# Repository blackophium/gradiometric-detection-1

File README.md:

# gradiometric-detection-1
Gradiometric detection of heart rate - analog model.

This is a project of PCB which includes:

- 10.7 MHZ sine generator (transmitting coil),
- place for receive a signal from receiver coil,
- synchronous demodulation,
- transmitting signal filtration.

How it works:

The generator transmits a signal to a transmitting coil, which is applied to the patient's chest. 
The carrier signal is received along with the wave signal from the mechanical operation of the heart through receiver coils arranged in an anti-parallel way. 
Then the signal is demodulated and filtered (we filter out the constant component of the carrier wave 10.7MHz). 

The resulting signal is a medium disturbance originating in the patient's chest.

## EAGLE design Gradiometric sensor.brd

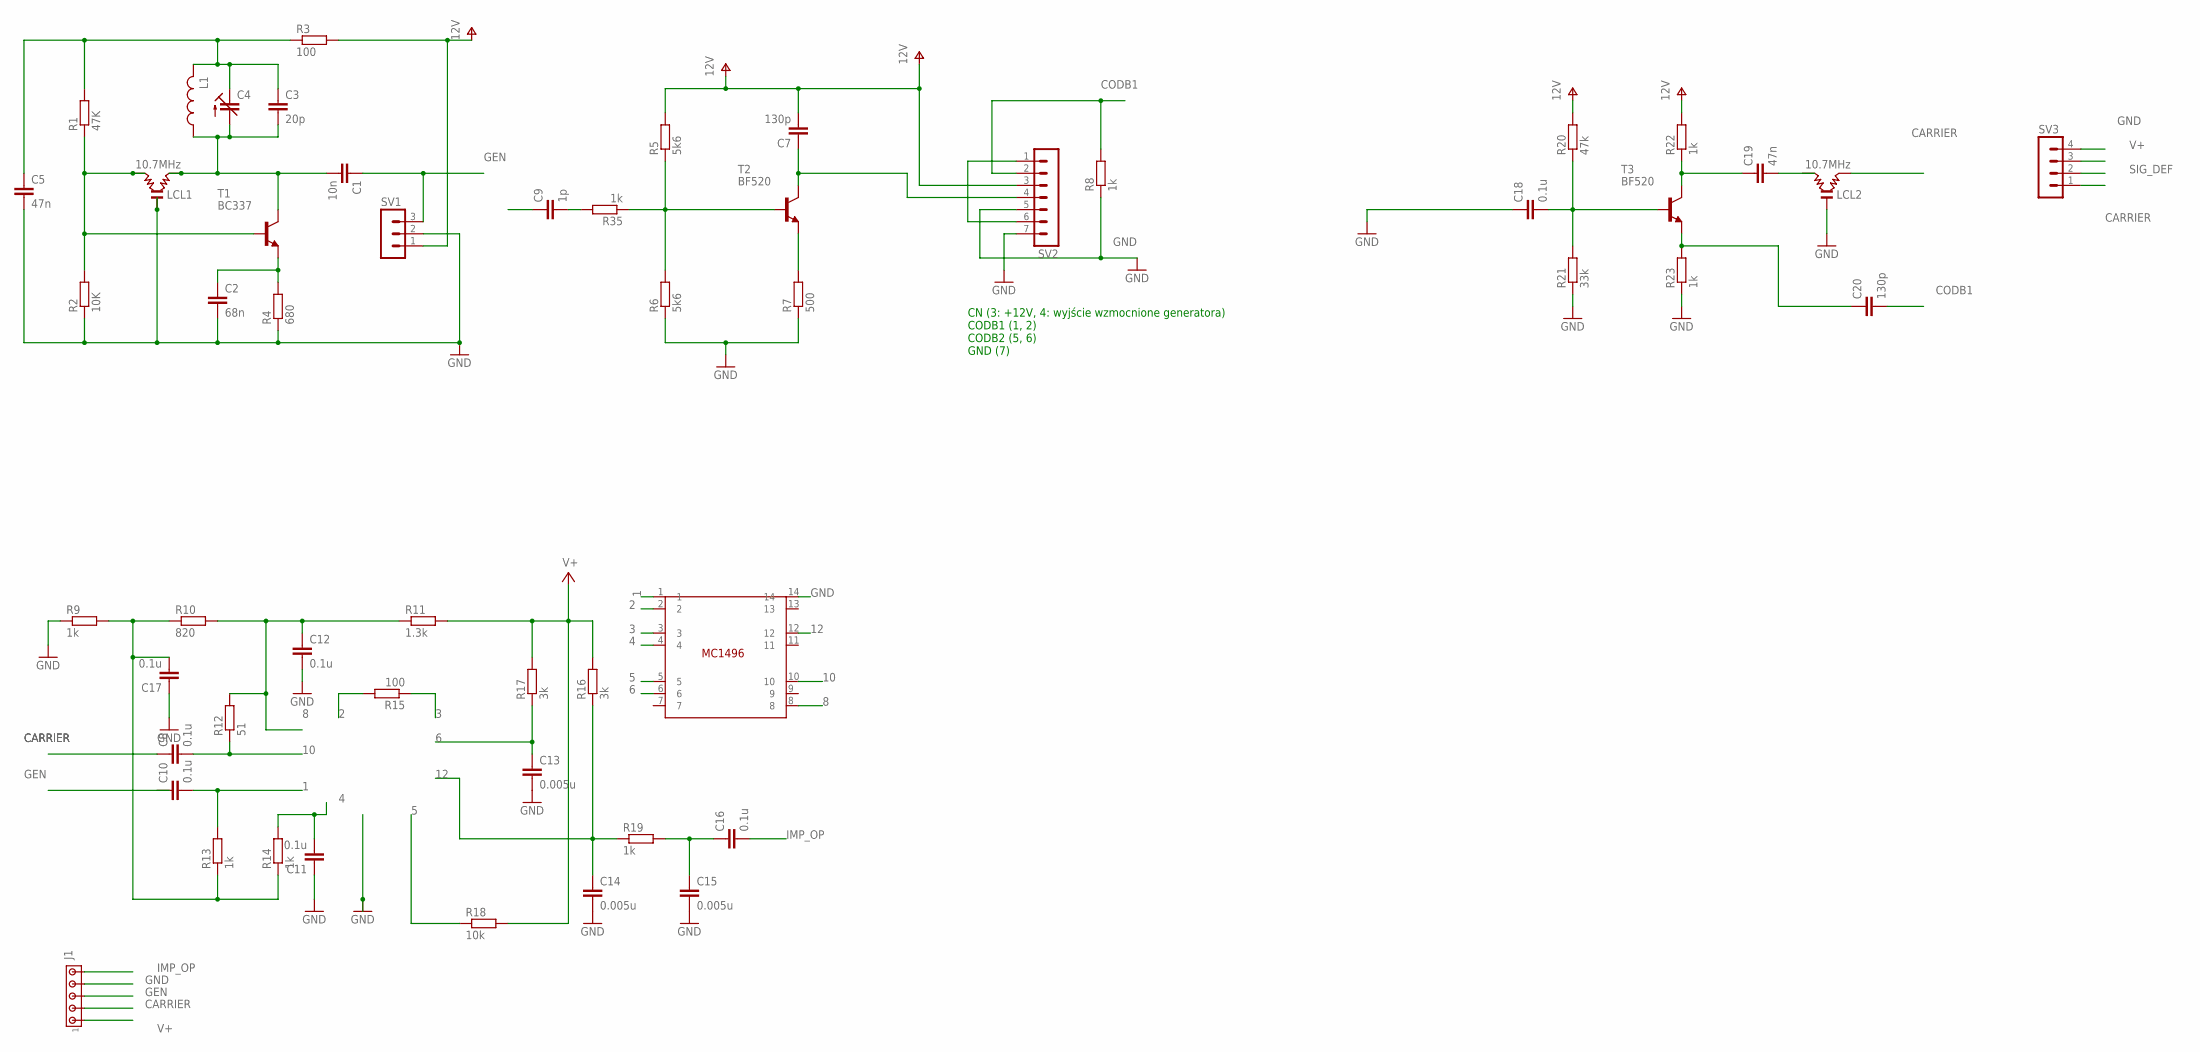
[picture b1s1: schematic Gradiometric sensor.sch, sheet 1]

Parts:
C1: 10n; C0805
C2: 68n; C0805
C3: 20p; C0805
C4: C-TRIMM808; CTRIM808-BC
C5, C19: 47n; C0805
C7, C20: 130p; C0805
C8, C10, C11, C12, C16, C17, C18: 0.1u; C0805
C9: 1p; C0805
C13, C14, C15: 0.005u; C0805
J1: MTA05-100; 10X05MTA
L1: L-USL1812; L1812
LCL1, LCL2: 10.7MHz; LCL
R1: 47K; R0805
R2: 10K; R0805
R3, R15: 100; R0805
R4: 680; R0805
R5, R6: 5k6; R0805
R7: 500; R0805
R8, R9, R13, R14, R19, R22, R23, R35: 1k; R0805
R10: 820; R0805
R11: 1.3k; R0805
R12: 51; R0805
R16, R17: 3k; R0805
R18: 10k; R0805
R20: 47k; R0805
R21: 33k; R0805
SV1: MA03-1
SV2: MA07-1
SV3: MA04-1
T1: BC337; TO92
T2, T3: BF520; TO92
U$1: MC1496; SO-14DW

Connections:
1: C10.2, R13.2, U$1.1
2: R15.2, U$1.2
3: R15.1, U$1.3
4: C11.2, R14.2, U$1.4
5: R18.1, U$1.5
6: C13.1, R17.1, U$1.6
8: C12.1, R10.2, R11.1, R12.2, U$1.8
10: C8.2, R12.1, U$1.10
12: C14.1, R16.1, R19.1, U$1.12
CARRIER: C8.1, J1.2, LCL2.2, SV3.1
CODB1: C20.2, R8.2, SV2.2
GEN: C1.1, C10.1, J1.3, SV1.3
GND: C2.2, C5.2, C11.1, C12.2, C13.2, C14.2, C15.2, C17.1, C18.1, J1.4, LCL1.0 (GND), LCL2.0 (GND), R2.1, R4.1, R6.1, R7.1, R8.1, R9.1, R21.1, R23.1, SV1.2, SV2.5, SV2.7, SV3.4, U$1.14; also elsewhere on the board
IMP_OP: C16.2, J1.5; also elsewhere on the board
unnamed: LCL1.1, R1.1, R2.2, T1.2 (B)
unnamed: C3.1, C4.1 (E), C5.1, L1.2, R1.2, R3.1
unnamed: C2.1, R4.2, T1.1 (E)
unnamed: R5.1, R6.2, R35.1, T2.2 (B)
unnamed: C1.2, C3.2, C4.2 (A), L1.1, LCL1.2, T1.3 (C)
unnamed: R7.2, T2.1 (E)
unnamed: C7.1, SV2.4, T2.3 (C)
unnamed: SV2.1, SV2.6
unnamed: C17.2, R9.2, R10.1, R13.1, R14.1
unnamed: C15.1, C16.1, R19.2
unnamed: C19.2, LCL2.1
unnamed: C18.2, R20.1, R21.2, T3.2 (B)
unnamed: C19.1, R22.1, T3.3 (C)
unnamed: C20.1, R23.2, T3.1 (E)
unnamed: C9.2, R35.2
SIG_DEF: SV3.2; also elsewhere on the board
V+: C7.2, J1.1, R3.2, R5.2, R11.2, R16.2, R17.2, R18.2, R20.2, R22.2, SV1.1, SV2.3, SV3.3; also elsewhere on the board

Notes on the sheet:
CN (3: +12V, 4: wyjście wzmocnione generatora) CODB1 (1, 2) CODB2 (5, 6) GND (7)

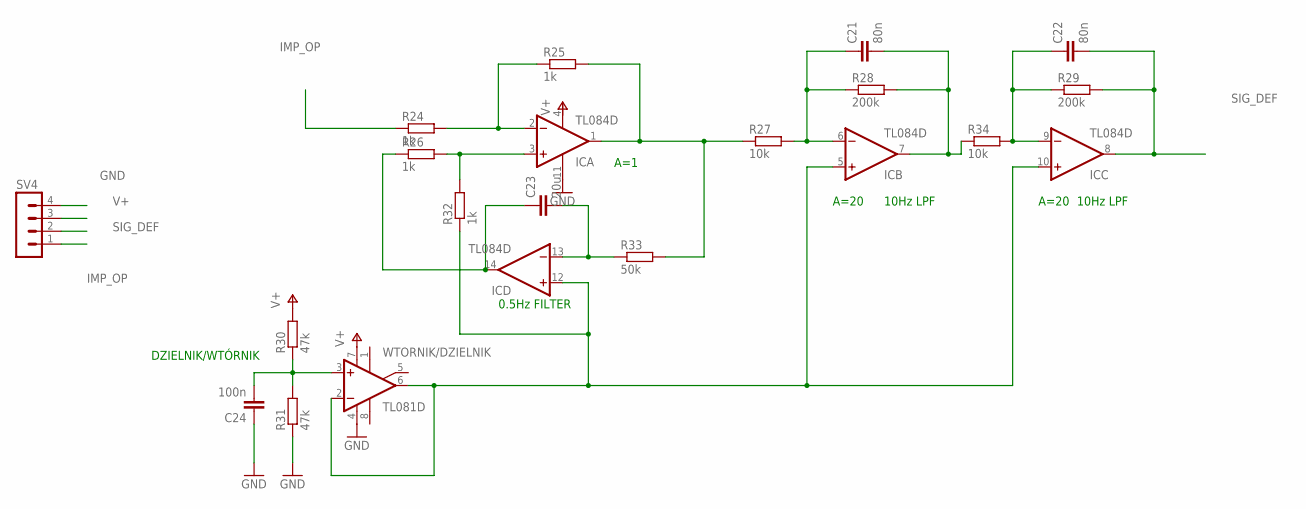
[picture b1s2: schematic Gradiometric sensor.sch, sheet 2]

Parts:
C21, C22: 80n; C0805
C23: 20u; C0805
C24: 100n; C0805
IC: TL084D; SO14
R24, R25, R26, R32: 1k; R0805
R27, R34: 10k; R0805
R28, R29: 200k; R0805
R30, R31: 47k; R0805
R33: 50k; R0805
SV4: MA04-1
WTORNIK/DZIELNIK: TL081D; SO08

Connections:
GND: C24.1, IC.11 (V-), R31.1, SV4.4, WTORNIK/DZIELNIK.4 (V-); also elsewhere on the board
IMP_OP: R24.1, SV4.1; also elsewhere on the board
unnamed: IC.2 (-IN), R24.2, R25.1
unnamed: IC.1 (OUT), R25.2, R27.1, R33.2
unnamed: IC.3 (+IN), R26.2, R32.2
unnamed: C23.1, IC.14 (OUT), R26.1
unnamed: C21.2, IC.7 (OUT), R28.2, R34.1
unnamed: C21.1, IC.6 (-IN), R27.2, R28.1
unnamed: IC.5 (+IN), IC.10 (+IN), IC.12 (+IN), R32.1, WTORNIK/DZIELNIK.2 (-IN), WTORNIK/DZIELNIK.6 (OUT)
unnamed: C23.2, IC.13 (-IN), R33.1
unnamed: C24.2, R30.1, R31.2, WTORNIK/DZIELNIK.3 (+IN)
unnamed: C22.1, IC.9 (-IN), R29.1, R34.2
SIG_DEF: C22.2, IC.8 (OUT), R29.2, SV4.2; also elsewhere on the board
V+: IC.4 (V+), R30.2, SV4.3, WTORNIK/DZIELNIK.7 (V+); also elsewhere on the board

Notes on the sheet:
DZIELNIK/WTÓRNIK
10Hz LPF
0.5Hz FILTER
A=1
A=20

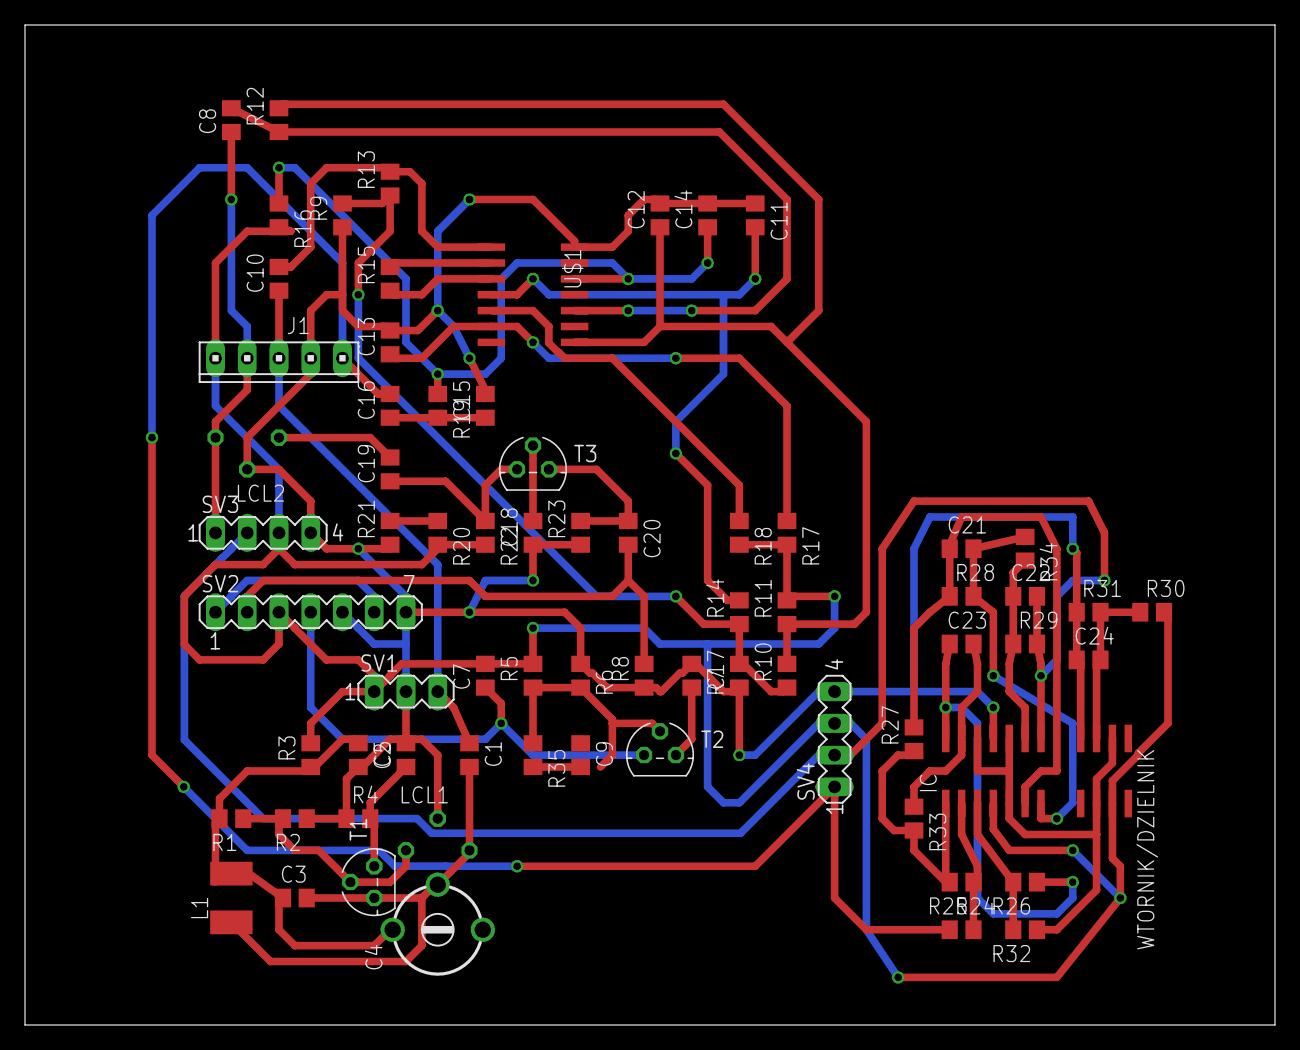
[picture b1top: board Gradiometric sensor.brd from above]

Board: 2 copper layers, 100.0 x 80.0 mm, 72 parts (0 on the bottom side), 41 nets.
